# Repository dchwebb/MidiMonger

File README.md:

<p align="center"></p>

# MidiMonger v2

MidiMonger is a Eurorack MIDI interface supporting USB and serial MIDI. 

MIDI Monger is a configurable MIDI interface for controlling Eurorack modules from either USB MIDI or Serial MIDI (or both simultaneously). MidiMonger 2 adds support for USB host functionality allowing the use of USB MIDI controllers (and experimentally USB HID mice) to control Eurorack modules.

MIDI Monger has 12 outputs of which 8 are gate outputs and 4 are control voltage outputs. The first eight outputs are configured by default as channel pairs. When assigned a MIDI channel they will act as a monophonic gate/cv driven from a single MIDI channel or in polyphonic mode supporting up to 4 note polyphony.

When not used in a pair a gate output can send a gate for any MIDI note from a channel, for a specific note number on a channel (eg for use as drum triggers) or a clock. The Control Voltage outputs can be configured to send controller data, pitch bend or aftertouch.

Configuration is carried out from a [web interface](https://htmlpreview.github.io/?https://github.com/dchwebb/MidiMonger/blob/master/WebEditor/index.html) using the Chrome browser or via a Virtual COM Port:

# USB
MidiMonger can act as either a USB device (typically for connection to a computer) or a USB Host (allowing USB Midi controllers to be connected). The mode is selected using a switch on the front panel and is connected with a USB-C socket.

In USB device mode USB MIDI data is merged with MIDI Serial data and sent to the CV and gate outputs as configured. In host mode USB devices can be connected directly to the module. This is typically used for MIDI keyboards and controllers that output via USB, but experimental support is also provided for USB HID devices - mouse support is currently implemented, but joysticks etc could be implemented in the future.

When connecting a USB mouse by default the left/right up/down and mouse wheel are output on CV 1, 2 and 3 and the buttons are output to the gates. This can be configured using the serial console.

In host mode the device will output 5v to power connected devices, but it is not recommended use with power hungry devices as the 5v rail is supplied via a linear regulator which has limited power output and also is used to supply a reference voltage to the DAC.

# Technical

MIDI Monger is controlled by an ARM STM32F446 Microcontroller. The MCU manages USB (device and host modes) and serial MIDI. Control voltages are output from a Maxim MAX5134 16 bit DAC controlled by SPI.

Gate outputs are converted to Eurorack standard of 5V using a SN74HCT244 Octal buffer as a level shifter. MIDI Serial signals are buffered through a 6N137 Optocoupler.

A UART connection is also provided to the module allowing access to the serial console when operating in USB host mode.

Serial MIDI is supplied via a 1/8" TRS jack using the MIDI standard wiring.

Digital power is supplied from a 3.3v linear regulator. An additional 5v regulator is used to supply a reference voltage to the DAC, as power for the octal buffer and also to provide power to USB devices when operating in USB Host mode.

The module is constructed using three PCBs: a component board, a control board and a panel. Schematics and PCB layout created in KiCad v8 and available in [Hardware folder](https://github.com/dchwebb/MidiMonger/tree/master/Hardware_v2).

[Components schematic](Hardware_v2/MidiMonger_Components.pdf)

[Controls schematic](Hardware_v2/MidiMonger_Controls.pdf)

# Errata (v2 hardware)
- The 3.3v linear regulator runs quite warm - some passive PCB cooling would be a good idea or possibly the use of a switched mode power supply (no analog voltages are supplied from this rail).
- A separate switched mode 5V rail would allow the connection of more power hungry USB devices without risking noise or sagging on the analog 5V reference.
- The USB device/host icons on the mode switch front panel should be swapped.
- To allow PWM brightmess control over the CV LEDs, CV1_LED and CV2_LED should be switched to pins lined to TIM4 (CV3_LED and CV4_LED connected to TIM4_CH2 and CH3)

# Version 1 Hardware

The original version of the module works with the latest firmware using the build in [V1 Hardware folder](https://github.com/dchwebb/MidiMonger/tree/master/MidiMonger2/v1Hardware). The main differences are that the v1 hardware does not support USB host mode, uses a full size MIDI DIN connector and a USB B socket.

Sponsorship
-----------

[PCBWay](https://www.pcbway.com/) were kind enough to sponsor the v2 module, manufacturing and supplying the three PCBs used for the component and control boards as well as the front panel. The quality of each PCB was excellent and the fine details were crisp and precise. Hand-soldering the fine-pitch components on the prototypes was extremely easy thanks to the high quality accuracy of the solder mask.

Many thanks to PCBWay for their generosity in sponsoring this project and their services come highly recommended.

<p align="center"></p>

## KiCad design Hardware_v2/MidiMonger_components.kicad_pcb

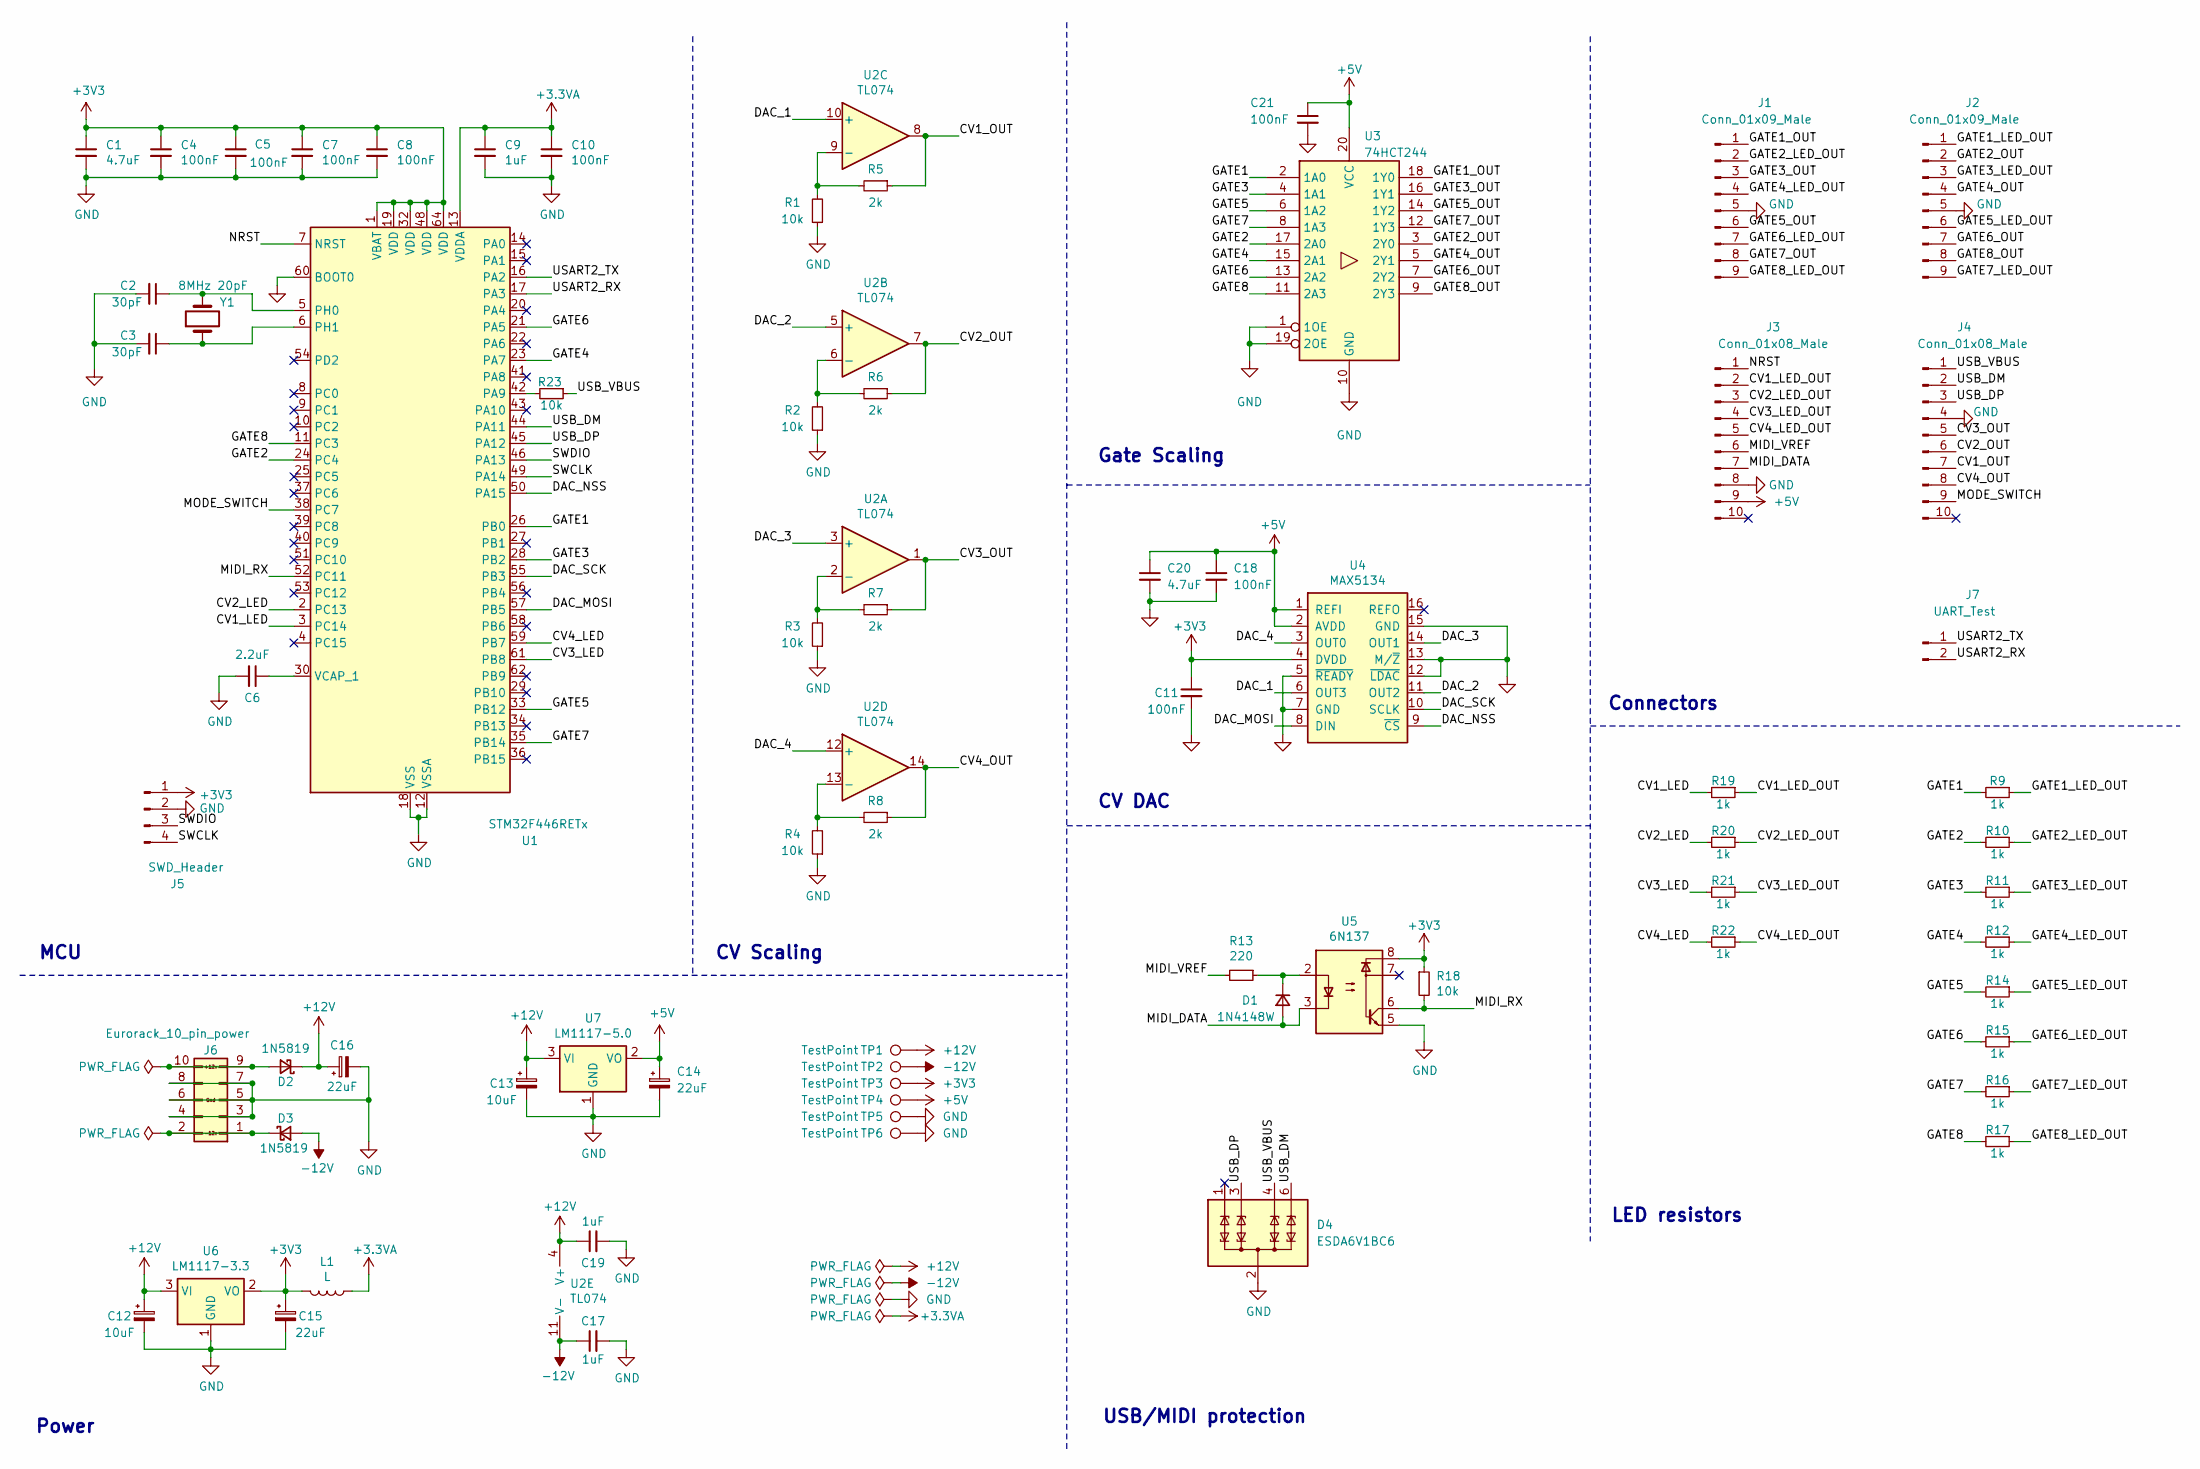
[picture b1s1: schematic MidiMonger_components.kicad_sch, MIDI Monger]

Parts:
C1, C20: 4.7uF; C_0603_1608Metric
C2, C3: 30pF; C_0603_1608Metric
C4, C5, C7, C8, C10, C11, C18, C21: 100nF; C_0603_1608Metric
C6: 2.2uF; C_0603_1608Metric
C9, C17, C19: 1uF; C_0603_1608Metric
C12, C13: 10uF; C_1206_3216Metric
C14, C15, C16: 22uF; CP_Elec_4x5.8
D1: 1N4148W; D_SOD-123
D2, D3: 1N5819; D_SOD-123
D4: ESDA6V1BC6; SOT-23-6
J1, J2: Conn_01x09_Male; PinHeader_1x09_P2.54mm_Vertical
J3, J4: Conn_01x08_Male; PinHeader_1x10_P2.54mm_Vertical
J5: SWD_Header; SWD_header
J6: Eurorack_10_pin_power; Eurorack_10_pin_header
J7: UART_Test; PinHeader_1x02_P2.54mm_Vertical
L1: L; L_0805_2012Metric_Pad1.05x1.20mm_HandSolder
R1, R2, R3, R4, R18, R23: 10k; R_0603_1608Metric
R5, R6, R7, R8: 2k; R_0603_1608Metric
R9, R10, R11, R12, R14, R15, R16, R17, R19, R20, R21, R22: 1k; R_0603_1608Metric
R13: 220; R_0603_1608Metric
TP1, TP2, TP3, TP4, TP5, TP6: TestPoint; 1mm_Test_Point
U1: STM32F446RETx; LQFP-64_10x10mm_P0.5mm
U2: TL074; SOIC-14_3.9x8.7mm_P1.27mm
U3: 74HCT244; TSSOP-20_4.4x6.5mm_P0.65mm
U4: MAX5134; TSSOP-16_4.4x5mm_P0.65mm
U5: 6N137; DIP-8_W8.89mm_SMDSocket_LongPads
U6: LM1117-3.3; SOT-223-3_TabPin2
U7: LM1117-5.0; SOT-223-3_TabPin2
Y1: 8MHz 20pF; Crystal_SMD_0603-2Pin_6.0x3.5mm; Part_Number C115962

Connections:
+3.3VA: C9.1, C10.1, L1.1, U1.13 (VDDA)
+3V3: C1.1, C4.1, C5.1, C7.1, C8.1, C11.1, C15.1, J5.1, L1.2, R18.1, TP3.1, U1.1 (VBAT), U1.19 (VDD), U1.32 (VDD), U1.48 (VDD), U1.64 (VDD), U4.4 (DVDD), U5.8, U6.2 (VO)
+5V: C14.1, C18.1, C20.1, C21.1, J3.9, TP4.1, U3.20 (VCC), U4.1 (REFI), U4.2 (AVDD), U7.2 (VO)
+12V: C12.1, C13.1, C16.1, C19.1, D2.1 (K), TP1.1, U2.4 (V+), U6.3 (VI), U7.3 (VI)
-12V: C17.1, D3.2 (A), TP2.1, U2.11 (V-)
/CV1_LED: R19.2, U1.3 (PC14)
/CV1_LED_OUT: J3.2, R19.1
/CV1_OUT: J4.7, R5.1, U2.8
/CV2_LED: R20.2, U1.2 (PC13)
/CV2_LED_OUT: J3.3, R20.1
/CV2_OUT: J4.6, R6.1, U2.7
/CV3_LED: R21.2, U1.61 (PB8)
/CV3_LED_OUT: J3.4, R21.1
/CV3_OUT: J4.5, R7.1, U2.1
/CV4_LED: R22.2, U1.59 (PB7)
/CV4_LED_OUT: J3.5, R22.1
/CV4_OUT: J4.8, R8.1, U2.14
/DAC_1: U2.10 (+), U4.6 (OUT3)
/DAC_2: U2.5 (+), U4.11 (OUT2)
/DAC_3: U2.3 (+), U4.14 (OUT1)
/DAC_4: U2.12 (+), U4.3 (OUT0)
/DAC_MOSI: U1.57 (PB5), U4.8 (DIN)
/DAC_NSS: U1.50 (PA15), U4.9 (~CS)
/DAC_SCK: U1.55 (PB3), U4.10 (SCLK)
/GATE1: R9.2, U1.26 (PB0), U3.2 (1A0)
/GATE1_LED_OUT: J2.1, R9.1
/GATE1_OUT: J1.1, U3.18 (1Y0)
/GATE2: R10.2, U1.24 (PC4), U3.17 (2A0)
/GATE2_LED_OUT: J1.2, R10.1
/GATE2_OUT: J2.2, U3.3 (2Y0)
/GATE3: R11.2, U1.28 (PB2), U3.4 (1A1)
/GATE3_LED_OUT: J2.3, R11.1
/GATE3_OUT: J1.3, U3.16 (1Y1)
/GATE4: R12.2, U1.23 (PA7), U3.15 (2A1)
/GATE4_LED_OUT: J1.4, R12.1
/GATE4_OUT: J2.4, U3.5 (2Y1)
/GATE5: R14.2, U1.33 (PB12), U3.6 (1A2)
/GATE5_LED_OUT: J2.6, R14.1
/GATE5_OUT: J1.6, U3.14 (1Y2)
/GATE6: R15.2, U1.21 (PA5), U3.13 (2A2)
/GATE6_LED_OUT: J1.7, R15.1
/GATE6_OUT: J2.7, U3.7 (2Y2)
/GATE7: R16.2, U1.35 (PB14), U3.8 (1A3)
/GATE7_LED_OUT: J2.9, R16.1
/GATE7_OUT: J1.8, U3.12 (1Y3)
/GATE8: R17.2, U1.11 (PC3), U3.11 (2A3)
/GATE8_LED_OUT: J1.9, R17.1
/GATE8_OUT: J2.8, U3.9 (2Y3)
/MIDI_DATA: D1.2 (A), J3.7, U5.3
/MIDI_RX: R18.2, U1.52 (PC11), U5.6
/MIDI_VREF: J3.6, R13.2
/MODE_SWITCH: J4.9, U1.38 (PC7)
/NRST: J3.1, U1.7 (NRST)
/SWCLK: J5.4, U1.49 (PA14)
/SWDIO: J5.3, U1.46 (PA13)
/USART2_RX: J7.2, U1.17 (PA3)
/USART2_TX: J7.1, U1.16 (PA2)
/USB_DM: D4.6 (TVS4), J4.2, U1.44 (PA11)
/USB_DP: D4.3 (TVS2), J4.3, U1.45 (PA12)
/USB_VBUS: D4.4 (TVS3), J4.1, R23.1
GND: C1.2, C2.2, C3.2, C4.2, C5.2, C6.2, C7.2, C8.2, C9.2, C10.2, C11.2, C12.2, C13.2, C14.2, C15.2, C16.2, C17.2, C18.2, C19.2, C20.2, C21.2, D4.2 (COM), D4.5 (COM), J1.5, J2.5, J3.8, J4.4, J5.2, J6.3, J6.4, J6.5, J6.6, J6.7, J6.8, R1.1, R2.1, R3.1, R4.1, TP5.1, TP6.1, U1.12 (VSSA), U1.18 (VSS), U1.31 (VSS), U1.47 (VSS), U1.60 (BOOT0), U1.63 (VSS), U3.1 (1OE), U3.10 (GND), U3.19 (2OE), U4.5 (~READY), U4.7 (GND), U4.12 (~LDAC), U4.13 (M/~Z), U4.15 (GND), U5.5, U6.1 (GND), U7.1 (GND)
unnamed: D1.1 (K), R13.1, U5.2
unnamed: D2.2 (A), J6.9, J6.10
unnamed: D3.1 (K), J6.1, J6.2
unnamed: R23.2, U1.42 (PA9)
unnamed: C2.1, U1.5 (PH0), Y1.2
unnamed: C3.1, U1.6 (PH1), Y1.1
unnamed: C6.1, U1.30 (VCAP_1)
unnamed: R3.2, R7.2, U2.2 (-)
unnamed: R2.2, R6.2, U2.6 (-)
unnamed: R1.2, R5.2, U2.9 (-)
unnamed: R4.2, R8.2, U2.13 (-)

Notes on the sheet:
CV DAC
LED resistors
Connectors
Gate Scaling
USB/MIDI protection
CV Scaling
Power
MCU

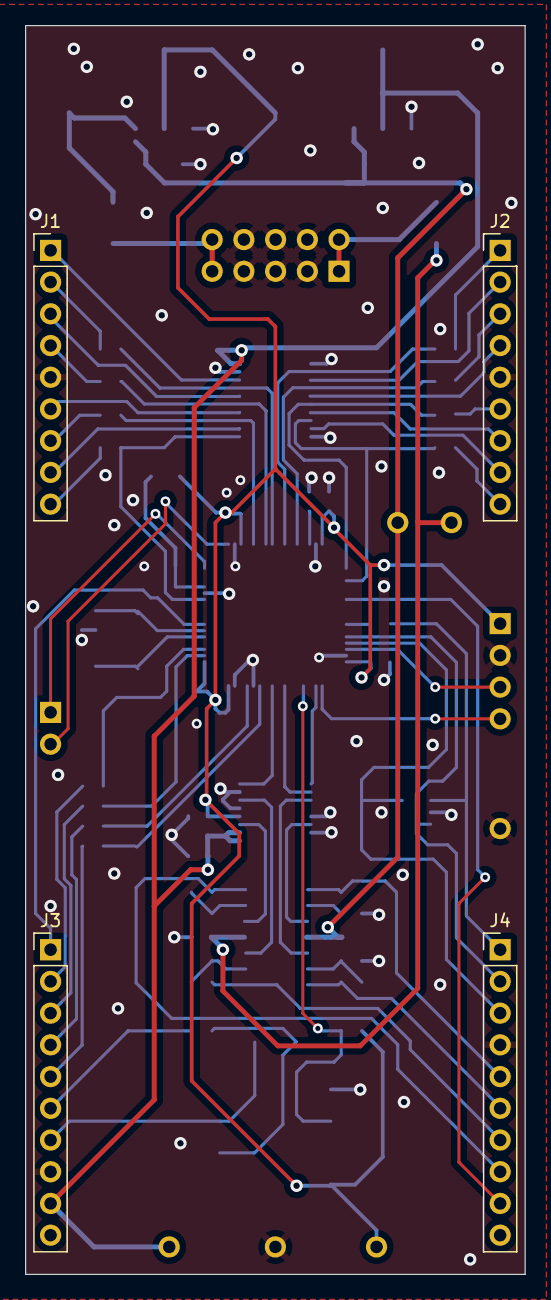
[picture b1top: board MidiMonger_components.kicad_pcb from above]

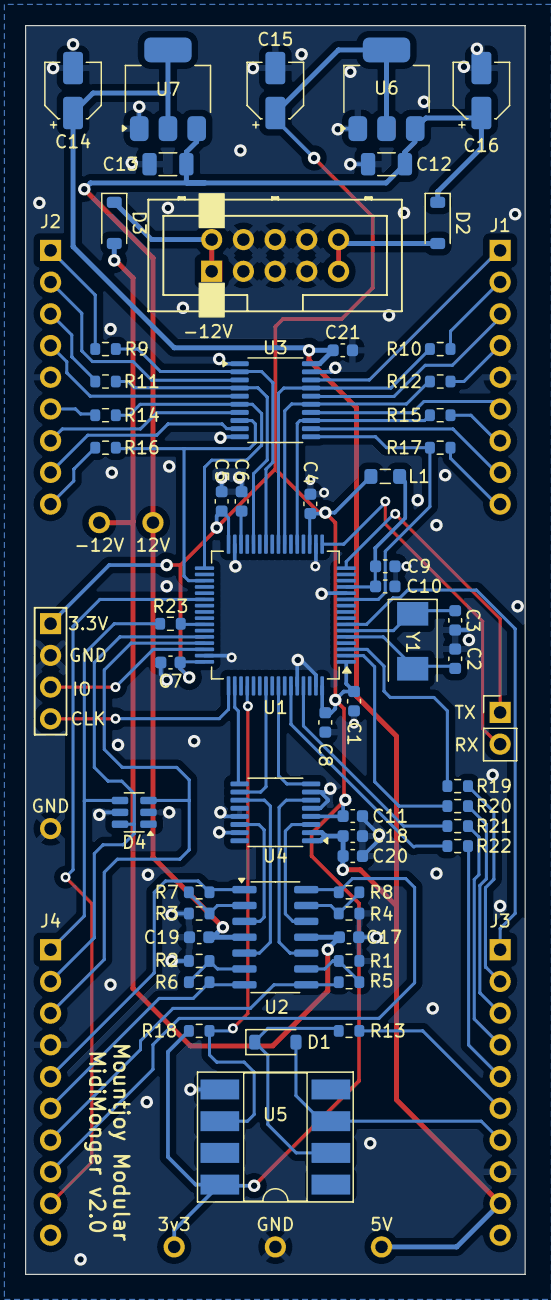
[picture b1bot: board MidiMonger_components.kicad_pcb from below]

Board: 2 copper layers, 40.0 x 100.0 mm, 70 parts (66 on the bottom side), 72 nets.

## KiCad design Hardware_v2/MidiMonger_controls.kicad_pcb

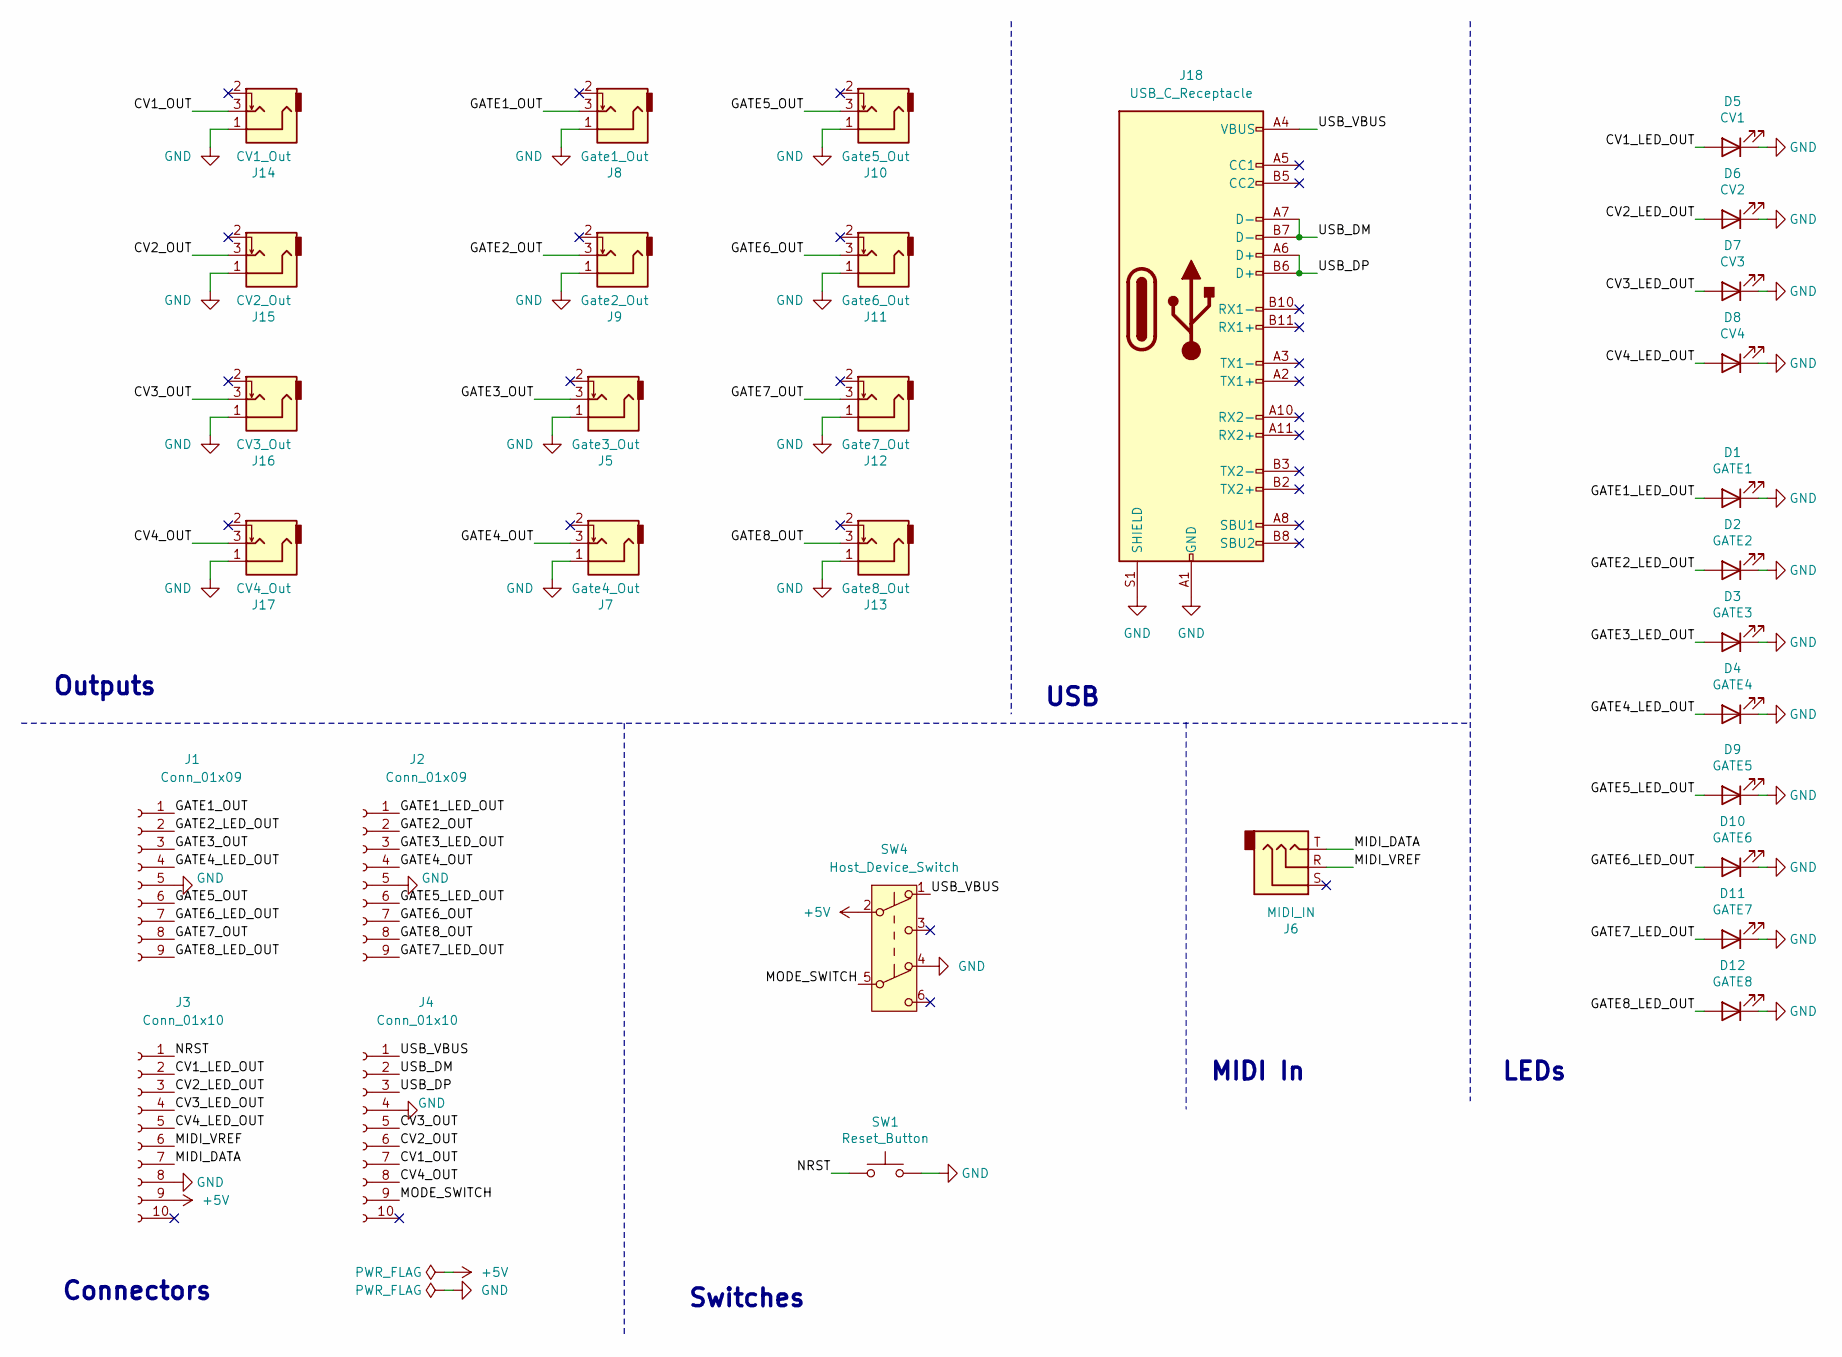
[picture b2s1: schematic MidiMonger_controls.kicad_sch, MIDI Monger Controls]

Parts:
D1: GATE1; LED_D3.0mm
D2: GATE2; LED_D3.0mm
D3: GATE3; LED_D3.0mm
D4: GATE4; LED_D3.0mm
D5: CV1; LED_D3.0mm
D6: CV2; LED_D3.0mm
D7: CV3; LED_D3.0mm
D8: CV4; LED_D3.0mm
D9: GATE5; LED_D3.0mm
D10: GATE6; LED_D3.0mm
D11: GATE7; LED_D3.0mm
D12: GATE8; LED_D3.0mm
J1, J2: Conn_01x09; PinSocket_1x09_P2.54mm_Vertical
J3, J4: Conn_01x10; PinSocket_1x10_P2.54mm_Vertical
J5: Gate3_Out; THONKICONN_hole
J6: MIDI_IN; Thonkiconn_Stereo-PJ366ST
J7: Gate4_Out; THONKICONN_hole
J8: Gate1_Out; THONKICONN_hole
J9: Gate2_Out; THONKICONN_hole
J10: Gate5_Out; THONKICONN_hole
J11: Gate6_Out; THONKICONN_hole
J12: Gate7_Out; THONKICONN_hole
J13: Gate8_Out; THONKICONN_hole
J14: CV1_Out; THONKICONN_hole
J15: CV2_Out; THONKICONN_hole
J16: CV3_Out; THONKICONN_hole
J17: CV4_Out; THONKICONN_hole
J18: USB_C_Receptacle; USB_C_Receptacle_Amphenol_12401951E412A
SW1: Reset_Button; SW_PUSH_6mm
SW4: Host_Device_Switch; 100DP6T1B1M2QE_ON_ON_ON

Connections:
+5V: J3.9, SW4.2 (B)
/CV1_LED_OUT: D5.2 (A), J3.2
/CV1_OUT: J4.7, J14.3
/CV2_LED_OUT: D6.2 (A), J3.3
/CV2_OUT: J4.6, J15.3
/CV3_LED_OUT: D7.2 (A), J3.4
/CV3_OUT: J4.5, J16.3
/CV4_LED_OUT: D8.2 (A), J3.5
/CV4_OUT: J4.8, J17.3
/GATE1_LED_OUT: D1.2 (A), J2.1
/GATE1_OUT: J1.1, J8.3
/GATE2_LED_OUT: D2.2 (A), J1.2
/GATE2_OUT: J2.2, J9.3
/GATE3_LED_OUT: D3.2 (A), J2.3
/GATE3_OUT: J1.3, J5.3
/GATE4_LED_OUT: D4.2 (A), J1.4
/GATE4_OUT: J2.4, J7.3
/GATE5_LED_OUT: D9.2 (A), J2.6
/GATE5_OUT: J1.6, J10.3
/GATE6_LED_OUT: D10.2 (A), J1.7
/GATE6_OUT: J2.7, J11.3
/GATE7_LED_OUT: D11.2 (A), J2.9
/GATE7_OUT: J1.8, J12.3
/GATE8_LED_OUT: D12.2 (A), J1.9
/GATE8_OUT: J2.8, J13.3
/MIDI_DATA: J3.7, J6.T
/MIDI_VREF: J3.6, J6.R
/MODE_SWITCH: J4.9, SW4.5 (B)
/NRST: J3.1, SW1.1
/USB_DM: J4.2, J18.A7 (D-), J18.B7 (D-)
/USB_DP: J4.3, J18.A6 (D+), J18.B6 (D+)
/USB_VBUS: J4.1, J18.A4 (VBUS), J18.A9 (VBUS), J18.B4 (VBUS), J18.B9 (VBUS), SW4.1 (A)
GND: D1.1 (K), D2.1 (K), D3.1 (K), D4.1 (K), D5.1 (K), D6.1 (K), D7.1 (K), D8.1 (K), D9.1 (K), D10.1 (K), D11.1 (K), D12.1 (K), J1.5, J2.5, J3.8, J4.4, J5.1, J7.1, J8.1, J9.1, J10.1, J11.1, J12.1, J13.1, J14.1, J15.1, J16.1, J17.1, J18.A1 (GND), J18.A12 (GND), J18.B1 (GND), J18.B12 (GND), J18.S1 (SHIELD), SW1.2, SW4.4 (A)

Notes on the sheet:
Outputs
Switches
USB
MIDI In
LEDs
Connectors

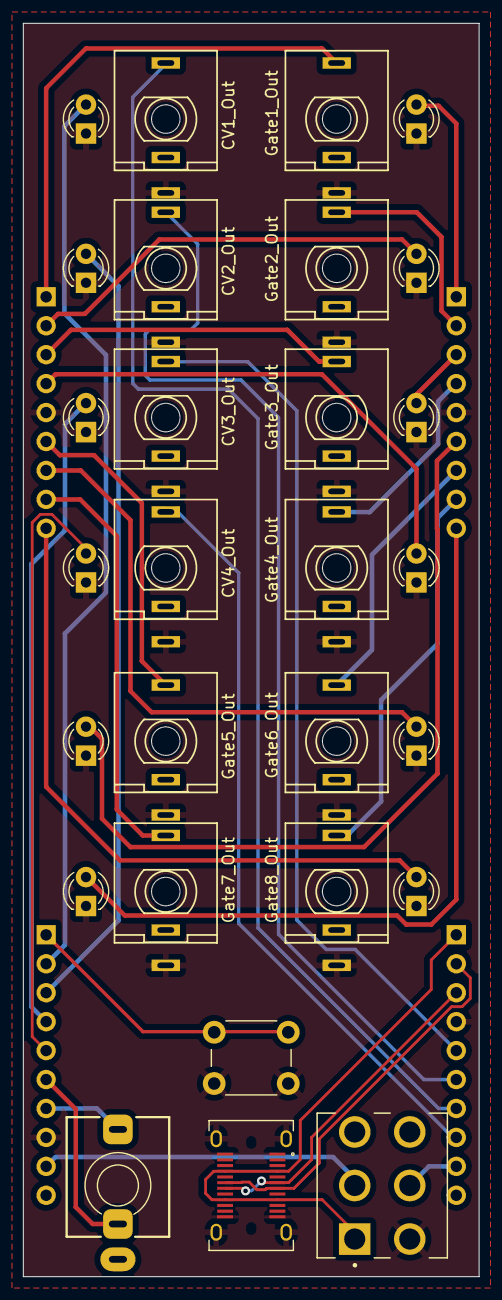
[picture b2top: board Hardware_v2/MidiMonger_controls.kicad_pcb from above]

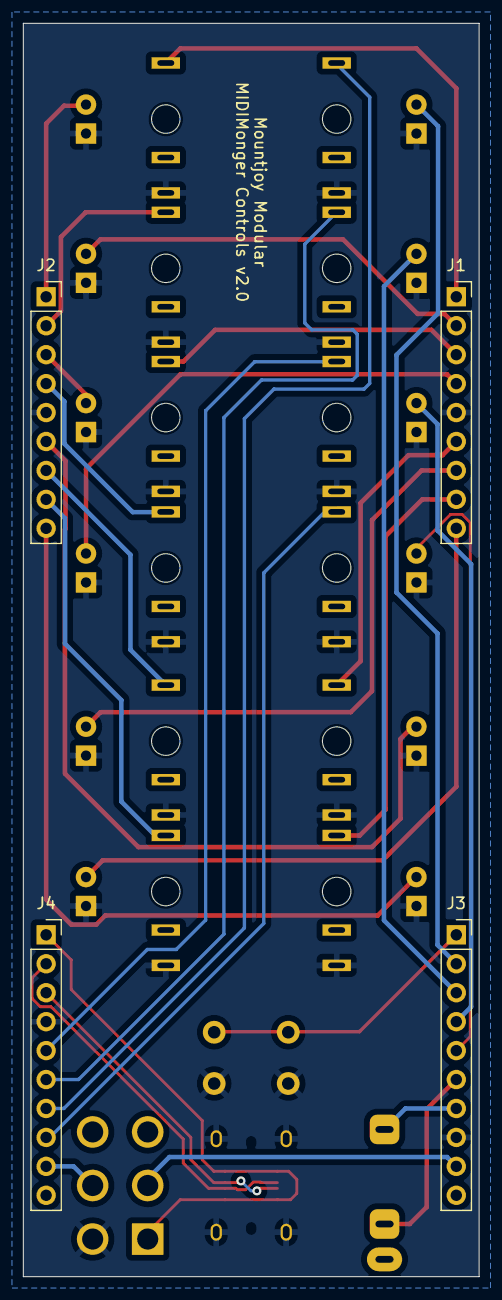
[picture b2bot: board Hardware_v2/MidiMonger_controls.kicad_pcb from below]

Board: 2 copper layers, 40.0 x 110.0 mm, 32 parts (4 on the bottom side), 33 nets.

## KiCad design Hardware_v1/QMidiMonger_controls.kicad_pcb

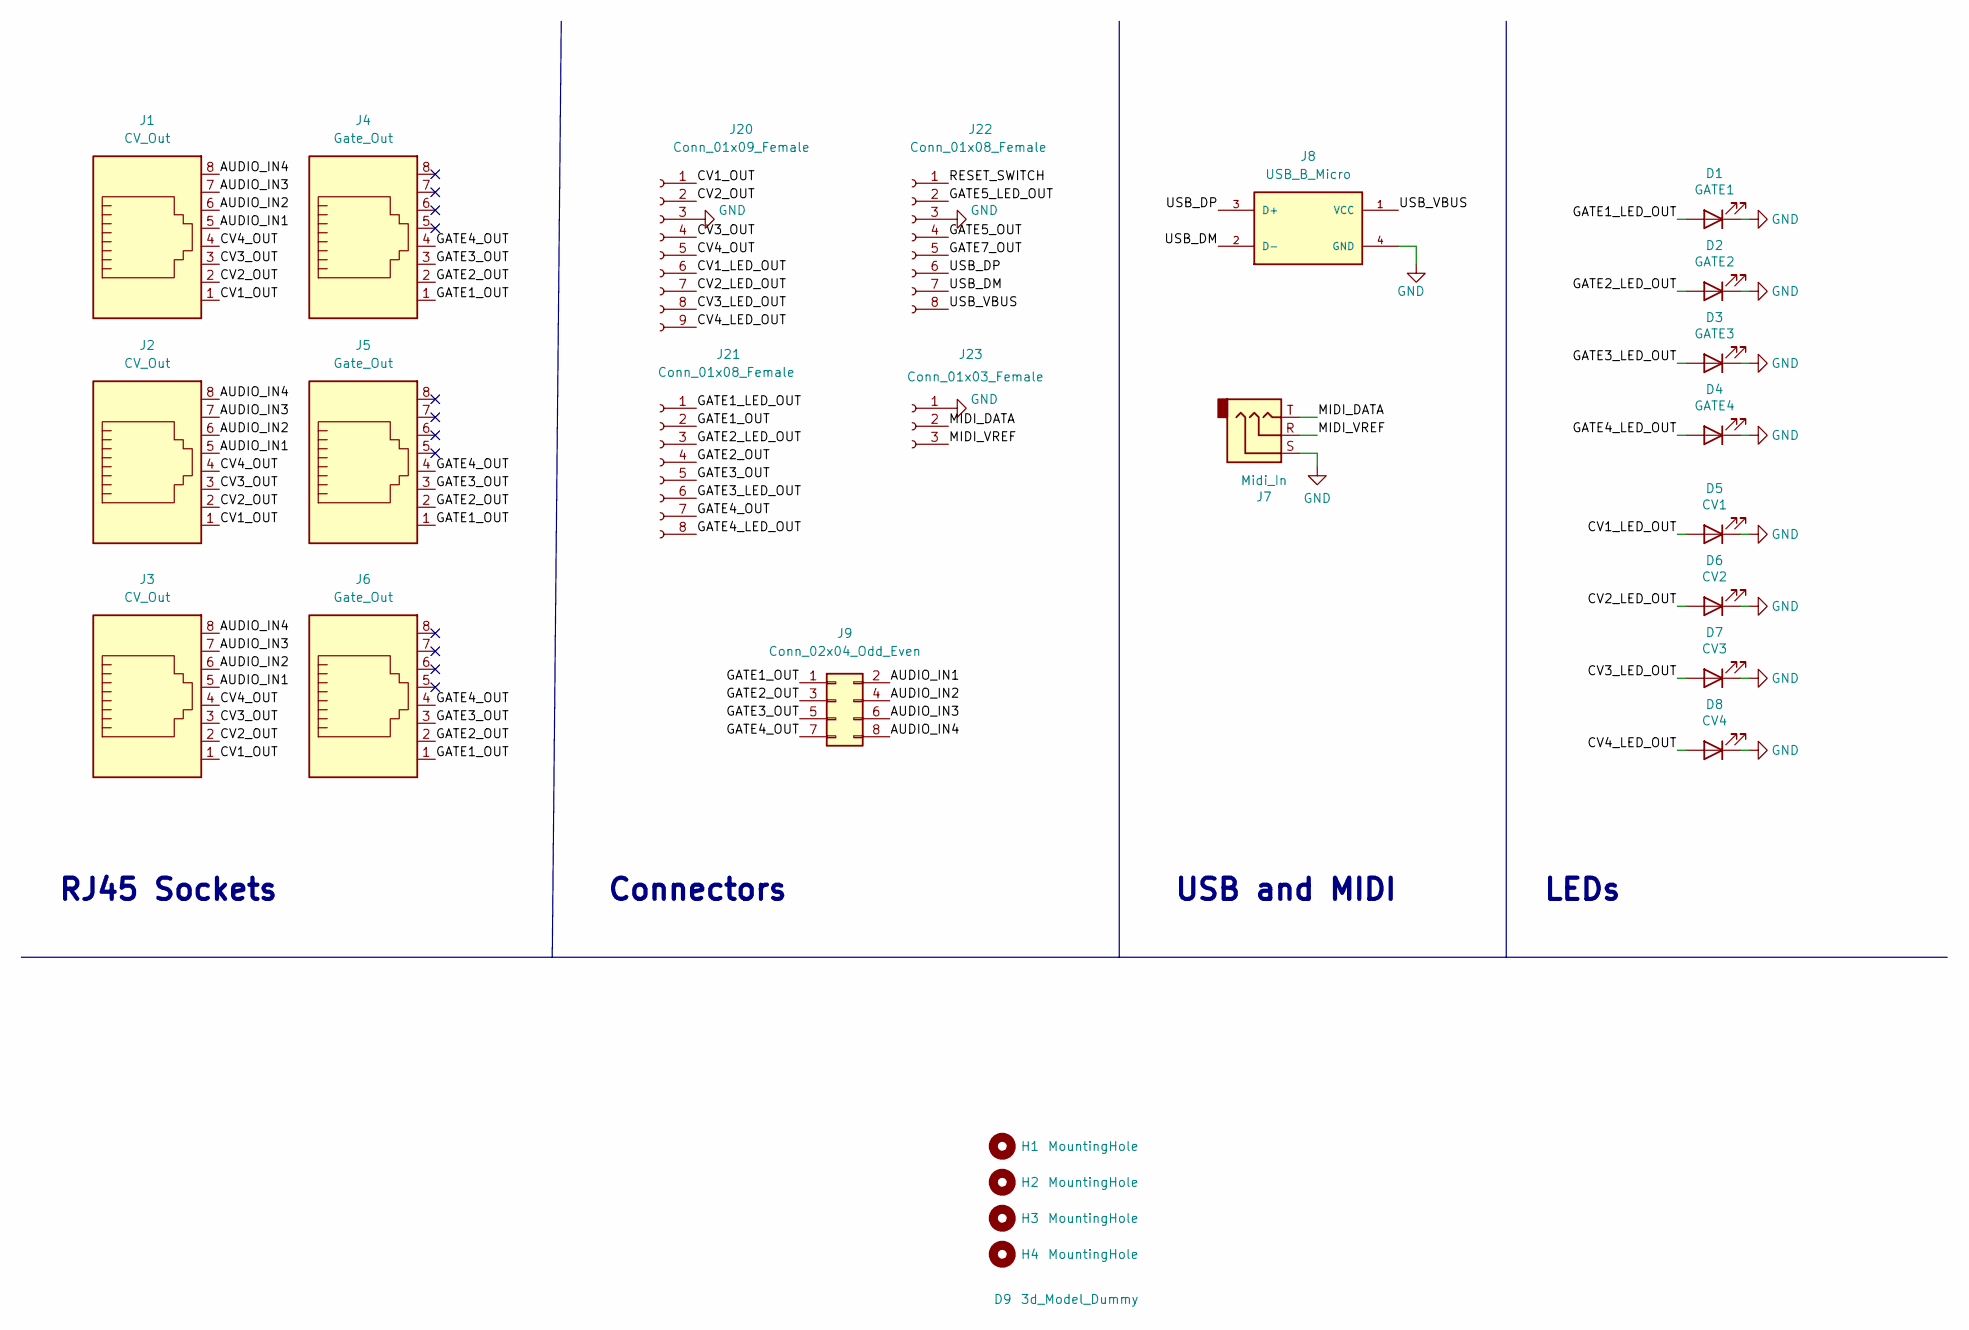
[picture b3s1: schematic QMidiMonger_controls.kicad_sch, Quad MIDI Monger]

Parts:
D1: GATE1; LED_D3.0mm
D2: GATE2; LED_D3.0mm
D3: GATE3; LED_D3.0mm
D4: GATE4; LED_D3.0mm
D5: CV1; LED_D3.0mm
D6: CV2; LED_D3.0mm
D7: CV3; LED_D3.0mm
D8: CV4; LED_D3.0mm
D9: 3d_Model_Dummy; 3D_Dummy
H1, H2, H3, H4: MountingHole; MountingHole_3.2mm_M3_ISO14580
J1, J2, J3: CV_Out; RJ45_Molex_42878-8506
J4, J5, J6: Gate_Out; RJ45_Molex_42878-8506
J7: Midi_In; Thonkiconn_Stereo-PJ366ST
J8: USB_B_Micro; USB_TE_1734517-1
J9: Conn_02x04_Odd_Even; PinHeader_2x04_P2.54mm_Vertical
J20: Conn_01x09_Female; Socket_Strip_Straight_1x09_Pitch2.54mm
J21, J22: Conn_01x08_Female; Socket_Strip_Straight_1x08_Pitch2.54mm
J23: Conn_01x03_Female; PinHeader_1x03_P2.54mm_Vertical

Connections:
/AUDIO_IN1: J1.5, J2.5, J3.5, J9.2
/AUDIO_IN2: J1.6, J2.6, J3.6, J9.4
/AUDIO_IN3: J1.7, J2.7, J3.7, J9.6
/AUDIO_IN4: J1.8, J2.8, J3.8, J9.8
/CV1_LED_OUT: D5.2 (A), J20.6
/CV1_OUT: J1.1, J2.1, J3.1, J20.1
/CV2_LED_OUT: D6.2 (A), J20.7
/CV2_OUT: J1.2, J2.2, J3.2, J20.2
/CV3_LED_OUT: D7.2 (A), J20.8
/CV3_OUT: J1.3, J2.3, J3.3, J20.4
/CV4_LED_OUT: D8.2 (A), J20.9
/CV4_OUT: J1.4, J2.4, J3.4, J20.5
/GATE1_LED_OUT: D1.2 (A), J21.1
/GATE1_OUT: J4.1, J5.1, J6.1, J9.1, J21.2
/GATE2_LED_OUT: D2.2 (A), J21.3
/GATE2_OUT: J4.2, J5.2, J6.2, J9.3, J21.4
/GATE3_LED_OUT: D3.2 (A), J21.6
/GATE3_OUT: J4.3, J5.3, J6.3, J9.5, J21.5
/GATE4_LED_OUT: D4.2 (A), J21.8
/GATE4_OUT: J4.4, J5.4, J6.4, J9.7, J21.7
/GATE5_LED_OUT: J22.2
/GATE5_OUT: J22.4
/GATE7_OUT: J22.5
/MIDI_DATA: J7.T, J23.2
/MIDI_VREF: J7.R, J23.3
/RESET_SWITCH: J22.1
/USB_DM: J8.2 (D-), J22.7
/USB_DP: J8.3 (D+), J22.6
/USB_VBUS: J8.1 (VCC), J22.8
GND: D1.1 (K), D2.1 (K), D3.1 (K), D4.1 (K), D5.1 (K), D6.1 (K), D7.1 (K), D8.1 (K), J7.S, J8.4 (GND), J20.3, J22.3, J23.1

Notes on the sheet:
RJ45 Sockets
LEDs
USB and MIDI
Connectors

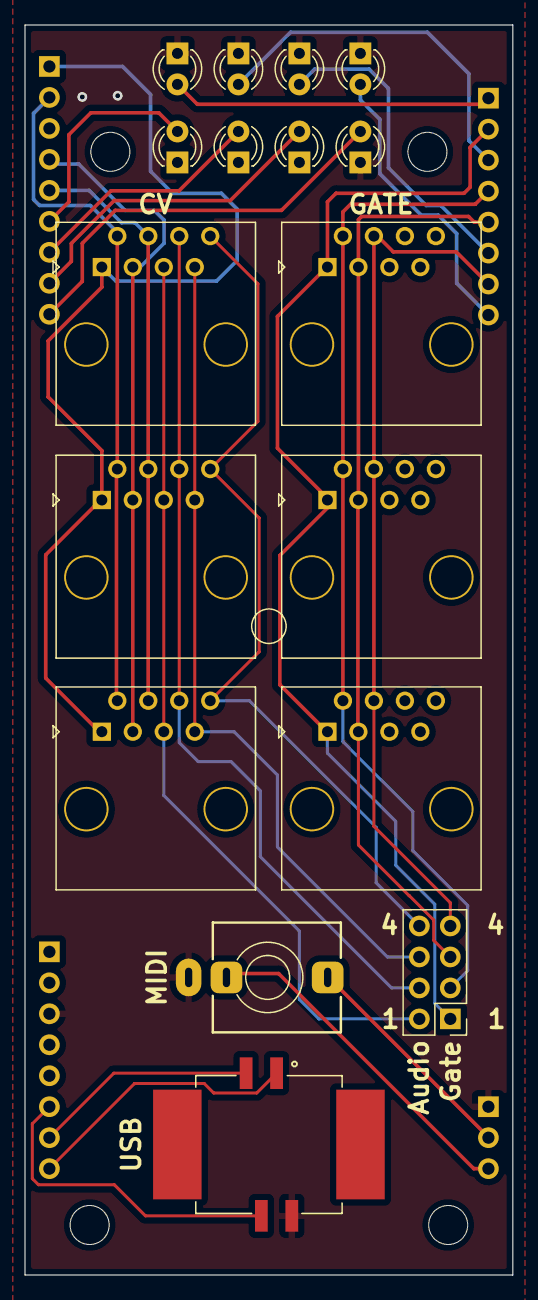
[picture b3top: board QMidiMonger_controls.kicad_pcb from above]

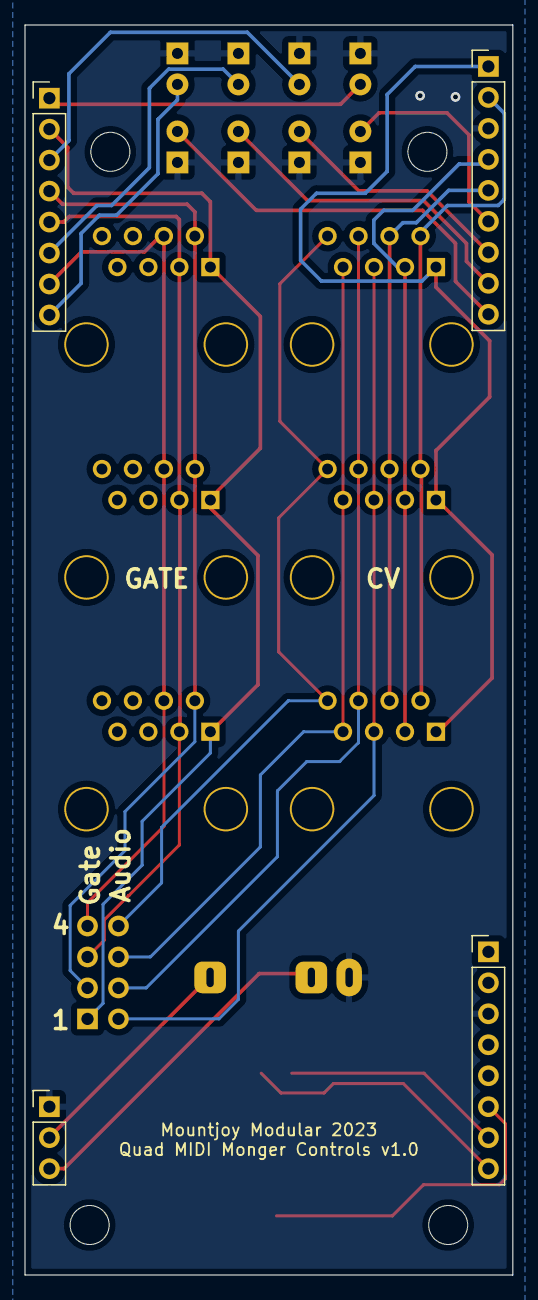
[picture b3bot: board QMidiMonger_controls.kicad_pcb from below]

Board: 2 copper layers, 40.0 x 102.5 mm, 26 parts (4 on the bottom side), 26 nets.

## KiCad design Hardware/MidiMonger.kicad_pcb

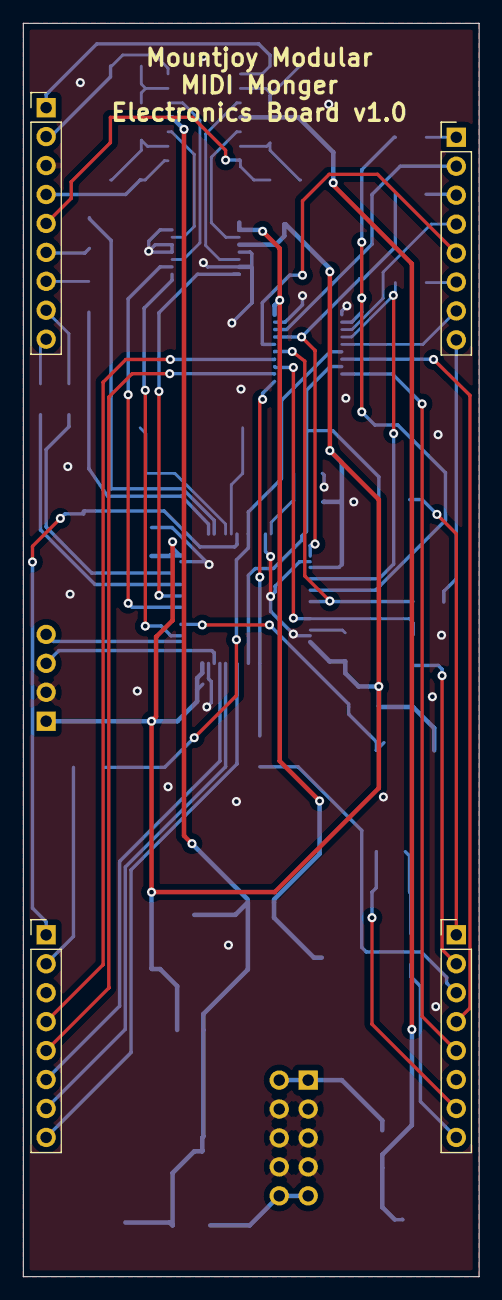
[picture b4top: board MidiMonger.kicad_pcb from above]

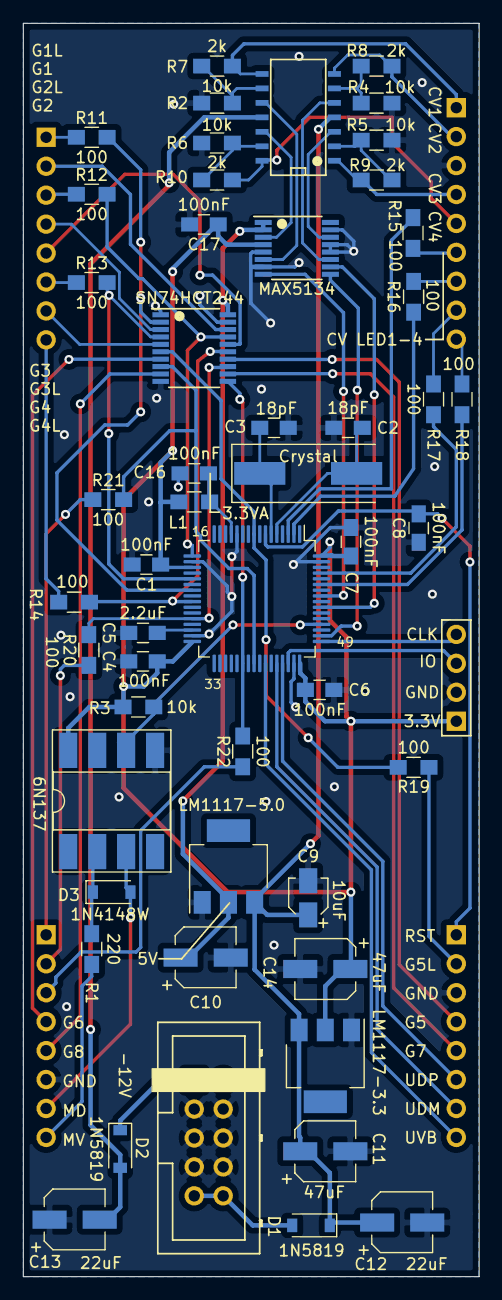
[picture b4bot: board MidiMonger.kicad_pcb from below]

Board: 2 copper layers, 40.0 x 110.0 mm, 56 parts (52 on the bottom side), 68 nets.

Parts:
C1, C4, C6, C7, C8, C16, C17: 100nF; C_0805_HandSoldering
C2, C3: 18pF; C_0805_HandSoldering
C5: 2.2uF; C_0805_HandSoldering
C9: 10uF; CP_Elec_3x5.3
C10, C12, C13: 22uF; CP_Elec_5x5.3
C11, C14: 47uF; CP_Elec_5x5.8
D1, D2: 1N5819; D_SOD-123
D3: 1N4148W; D_SOD-123
J1: SWD_Header; SWD_header
J2: Conn_01x09_Male; Socket_Strip_Straight_1x09_Pitch2.54mm
J3, J4, J5: Conn_01x08_Male; Socket_Strip_Straight_1x08_Pitch2.54mm
J9: Eurorack_10_pin_power; Eurorack_10_pin_header
L1: L; L_0805_HandSoldering
R1: 220; R_0805_HandSoldering
R2, R3, R4, R5, R6: 10k; R_0805_HandSoldering
R7, R8, R9, R10: 2k; R_0805_HandSoldering
R11, R12, R13, R14, R15, R16, R17, R18, R19, R20, R21, R22: 100; R_0805_HandSoldering
U1: STM32F446RETx; LQFP-64_10x10mm_P0.5mm
U2: 6N137; DIP-8_W8.89mm_SMDSocket_LongPads
U3: TL074; SOIC-14_N
U4: LM1117-5.0; SOT-223
U5: LM1117-3.3; SOT-223
U6: SN74HCT244; TSSOP-20_4.4x6.5mm_Pitch0.65mm
U7: MAX5134; TSSOP-16_4.4x5mm_Pitch0.65mm
Y1: Crystal; Crystal_SMD

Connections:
+3.3VA: C16.1, L1.1, U1.13
+3V3: C1.1, C4.1, C6.1, C7.1, C14.1, C17.1, J1.1, L1.2, R3.1, U1.19, U1.32, U1.48, U1.64, U2.8, U5.2, U7.4
+5V: C10.1, U4.2, U6.20, U7.1, U7.2
+12V: D1.2, J9.9, J9.10
-12V: D2.1, J9.1, J9.2
CV1_LED: R15.2, U1.3
CV1_LED_OUT: J2.6, R15.1
CV1_OUT: J2.1, R7.1, U3.8
CV2_LED: R16.2, U1.2
CV2_LED_OUT: J2.7, R16.1
CV2_OUT: J2.2, R8.1, U3.7
CV3_LED: R17.2, U1.61
CV3_LED_OUT: J2.8, R17.1
CV3_OUT: J2.4, R9.1, U3.1
CV4_LED: R18.2, U1.59
CV4_LED_OUT: J2.9, R18.1
CV4_OUT: J2.5, R10.1, U3.14
DAC_1: U3.10, U7.6
DAC_2: U3.5, U7.11
DAC_3: U3.3, U7.14
DAC_4: U3.12, U7.3
DAC_MOSI: U1.57, U7.8
DAC_NSS: U1.50, U7.9
DAC_SCK: U1.55, U7.10
GATE1: R11.2, U1.23, U6.2
GATE1_LED_OUT: J3.1, R11.1
GATE1_OUT: J3.2, U6.18
GATE2: R12.2, U1.17, U6.17
GATE2_LED_OUT: J3.3, R12.1
GATE2_OUT: J3.4, U6.3
GATE3: R13.2, U1.21, U6.4
GATE3_LED_OUT: J3.6, R13.1
GATE3_OUT: J3.5, U6.16
GATE4: R14.2, U1.25, U6.15
GATE4_LED_OUT: J3.8, R14.1
GATE4_OUT: J3.7, U6.5
GATE5: R19.2, U1.9, U6.6
GATE5_LED_OUT: J4.2, R19.1
GATE5_OUT: J4.4, U6.14
GATE6: R20.2, U1.28, U6.13
GATE6_LED_OUT: J5.2, R20.1
GATE6_OUT: J5.4, U6.7
GATE7: R21.2, U1.40, U6.8
GATE7_LED_OUT: J5.1, R21.1
GATE7_OUT: J4.5, U6.12
GATE8: R22.2, U1.38, U6.11
GATE8_LED_OUT: J5.3, R22.1
GATE8_OUT: J5.5, U6.9
GND: C1.2, C2.2, C3.2, C4.2, C5.2, C6.2, C7.2, C8.1, C9.2, C10.2, C11.2, C12.2, C13.1, C14.2, C16.2, C17.2, J1.2, J2.3, J4.3, J5.6, J9.3, J9.4, J9.5, J9.6, J9.7, J9.8, R2.1, R4.1, R5.1, R6.1, U1.12, U1.18, U1.31, U1.47, U1.63, U2.5, U4.1, U5.1, U6.1, U6.10, U6.19, U7.5, U7.7, U7.12, U7.13, U7.15
MIDI_DATA: D3.2, J5.7, U2.3
MIDI_RX: R3.2, U1.52, U2.6
MIDI_VREF: J5.8, R1.2
NRST: C8.2, J4.1, U1.7
unnamed: C2.1, U1.5, Y1.2
unnamed: C3.1, U1.6, Y1.1
unnamed: C5.1, U1.30
unnamed: D3.1, R1.1, U2.2
unnamed: R2.2, R7.2, U3.9
unnamed: R4.2, R8.2, U3.6
unnamed: R5.2, R9.2, U3.2
unnamed: R6.2, R10.2, U3.13
SWCLK: J1.4, U1.49
SWDIO: J1.3, U1.46
USB_DM: J4.7, U1.44
USB_DP: J4.6, U1.45
USB_VBUS: J4.8, U1.42
VCC: C9.1, C11.1, C12.1, D1.1, U3.4, U4.3, U5.3
VEE: C13.2, D2.2, U3.11
